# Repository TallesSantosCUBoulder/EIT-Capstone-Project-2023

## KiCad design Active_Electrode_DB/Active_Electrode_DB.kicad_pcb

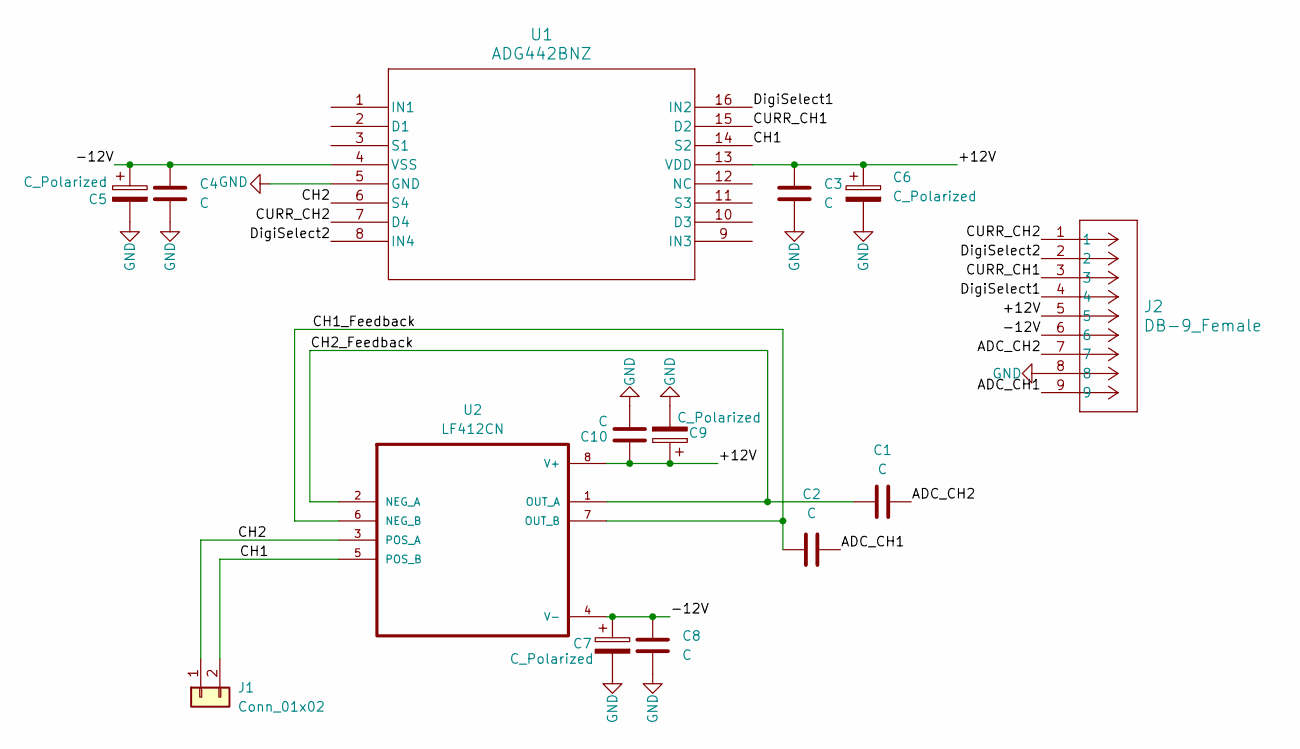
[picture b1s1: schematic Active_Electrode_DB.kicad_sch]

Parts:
C1, C3, C4, C8, C10: C; C_Disc_D4.3mm_W1.9mm_P5.00mm
C2: C; C_Disc_D6.0mm_W2.5mm_P5.00mm
C5, C6, C7, C9: C_Polarized; C_Disc_D4.3mm_W1.9mm_P5.00mm
J1: Conn_01x02; PinSocket_1x02_P2.54mm_Vertical
J2: DB-9_Female
U1: ADG442BNZ; N_16_ADI
U2: LF412CN

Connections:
/+12V: C3.1, C6.1, C9.1, C10.1, J2.5, U1.13 (VDD), U2.8 (V+)
/-12V: C4.1, C5.1, C7.1, C8.1, J2.6, U1.4 (VSS), U2.4 (V-)
/ADC_CH1: C2.2, J2.9
/ADC_CH2: C1.2, J2.7
/CH1: J1.2, U1.14 (S2), U2.5 (POS_B)
/CH1_Feedback: C2.1, U2.6 (NEG_B), U2.7 (OUT_B)
/CH2: J1.1, U1.6 (S4), U2.3 (POS_A)
/CH2_Feedback: C1.1, U2.1 (OUT_A), U2.2 (NEG_A)
/CURR_CH1: J2.3, U1.15 (D2)
/CURR_CH2: J2.1, U1.7 (D4)
/DigiSelect1: J2.4, U1.16 (IN2)
/DigiSelect2: J2.2, U1.8 (IN4)
GND: C3.2, C4.2, C5.2, C6.2, C7.2, C8.2, C9.2, C10.2, J2.8, U1.5 (GND)

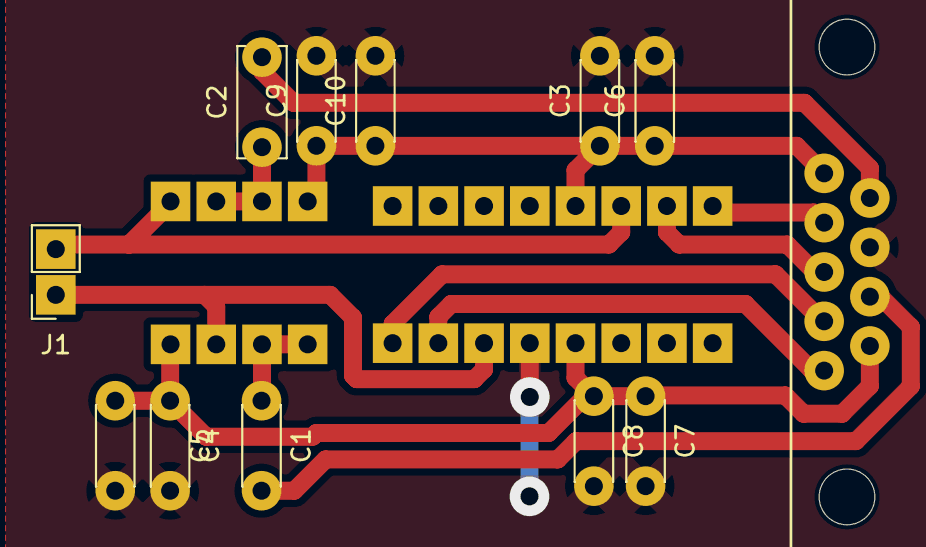
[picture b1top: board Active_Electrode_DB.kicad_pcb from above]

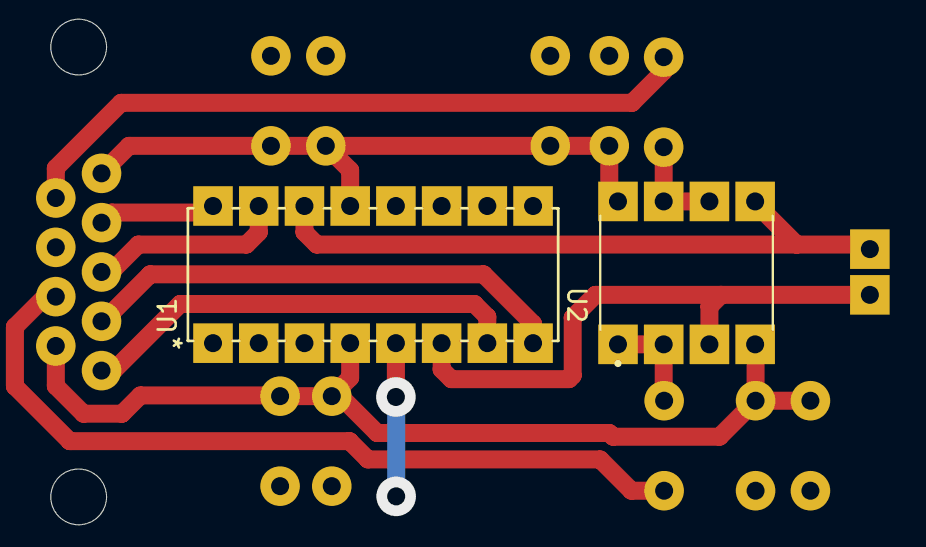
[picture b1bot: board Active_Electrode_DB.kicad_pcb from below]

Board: 2 copper layers, 14 parts (2 on the bottom side), 13 nets.

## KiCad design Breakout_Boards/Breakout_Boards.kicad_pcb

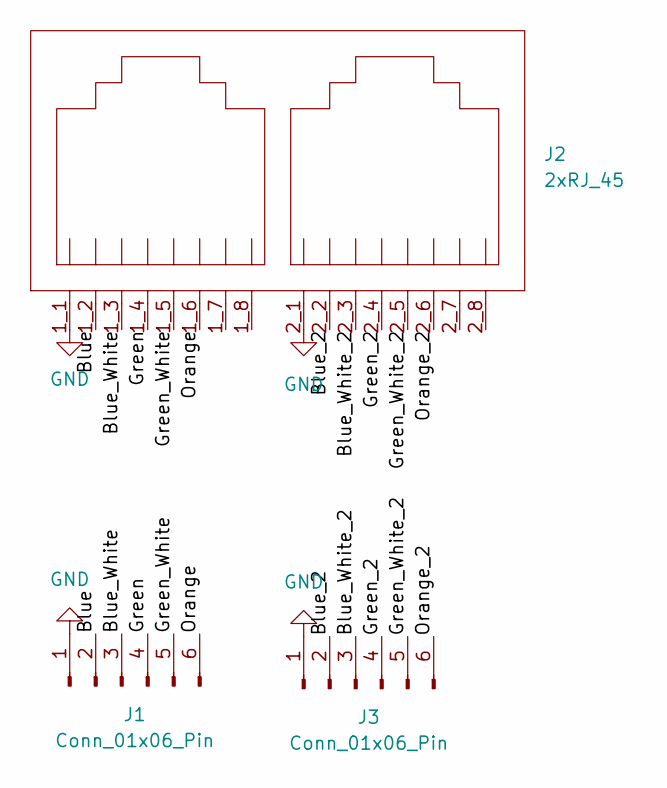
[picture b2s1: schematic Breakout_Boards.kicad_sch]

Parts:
J1, J3: Conn_01x06_Pin; PinSocket_1x06_P2.54mm_Vertical
J2: 2xRJ_45; TE_2xRJ45

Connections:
/Ethernet_Breakout/Blue: J1.2, J2.1_2
/Ethernet_Breakout/Blue_2: J2.2_2, J3.2
/Ethernet_Breakout/Blue_White: J1.3, J2.1_3
/Ethernet_Breakout/Blue_White_2: J2.2_3, J3.3
/Ethernet_Breakout/Green: J1.4, J2.1_4
/Ethernet_Breakout/Green_2: J2.2_4, J3.4
/Ethernet_Breakout/Green_White: J1.5, J2.1_5
/Ethernet_Breakout/Green_White_2: J2.2_5, J3.5
/Ethernet_Breakout/Orange: J1.6, J2.1_6
/Ethernet_Breakout/Orange_2: J2.2_6, J3.6
GND: J1.1, J2.1_1, J2.2_1, J3.1

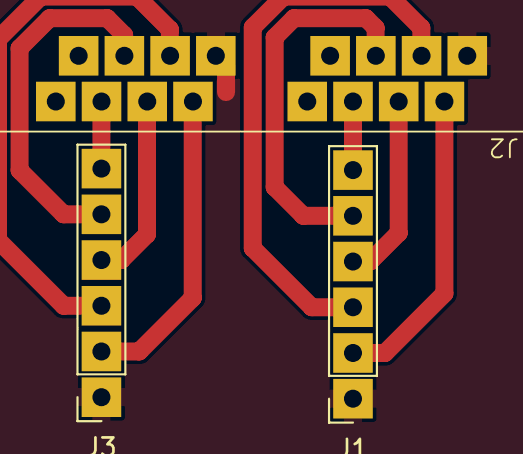
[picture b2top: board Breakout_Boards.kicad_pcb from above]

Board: 2 copper layers, 3 parts (0 on the bottom side), 11 nets.

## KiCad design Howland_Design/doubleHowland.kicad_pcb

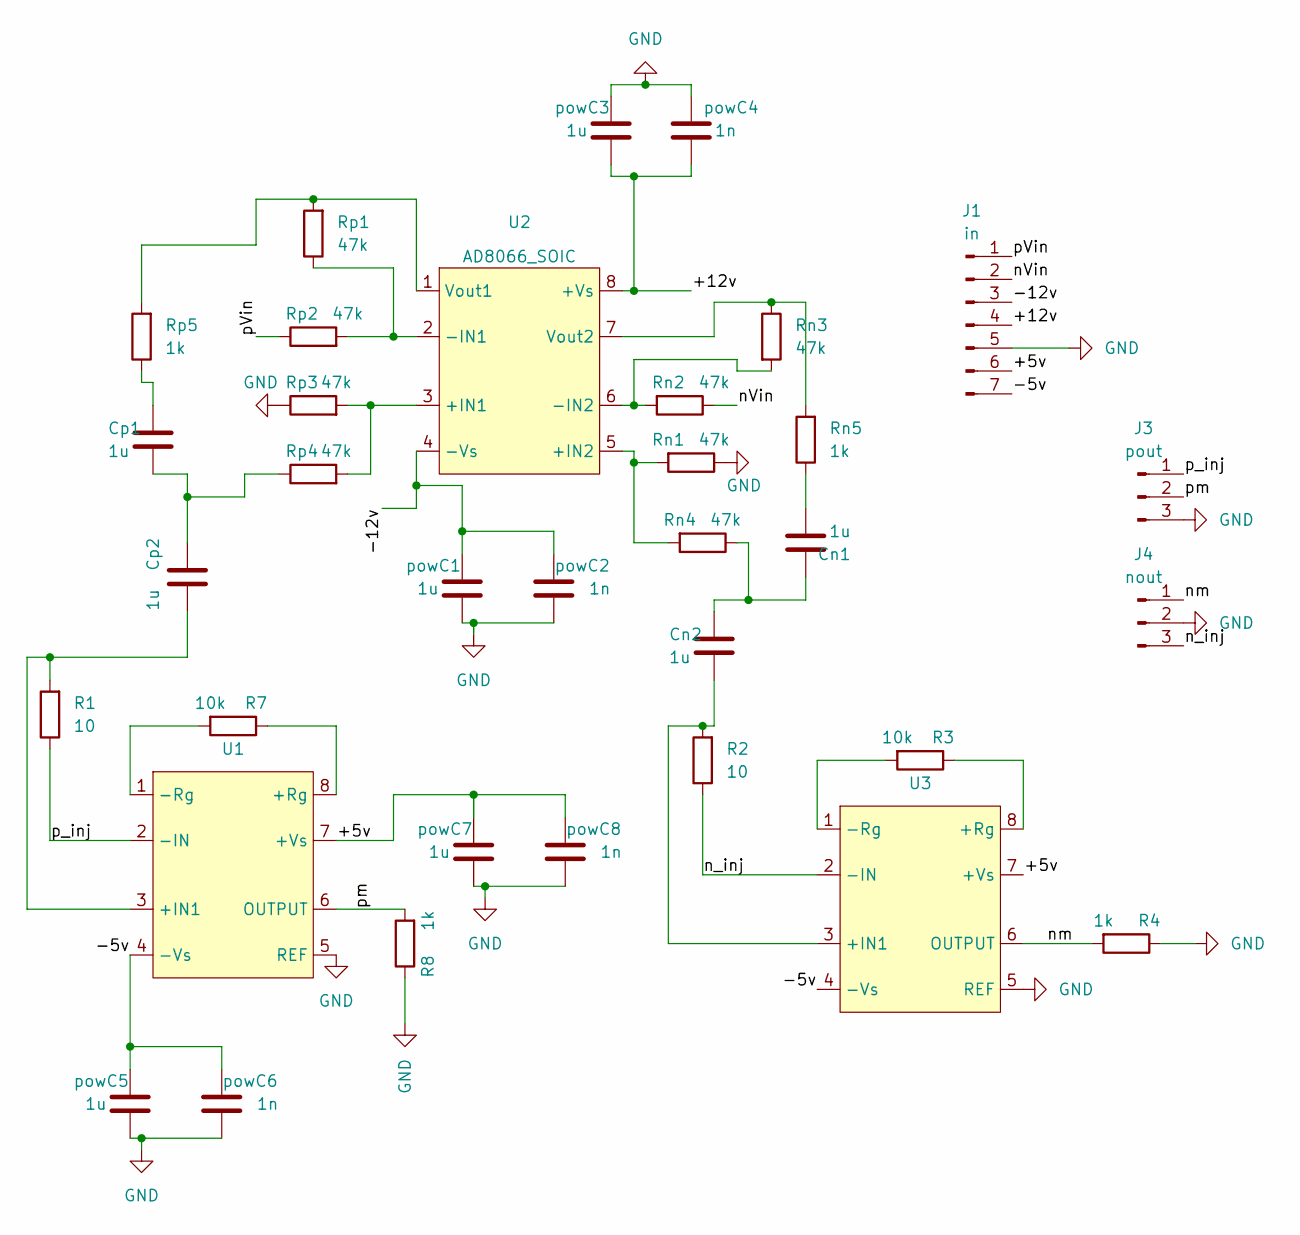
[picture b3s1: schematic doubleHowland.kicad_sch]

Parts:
Cn1, Cn2: 1u; R_Axial_DIN0207_L6.3mm_D2.5mm_P7.62mm_Horizontal
Cp1, Cp2: 1u; R_Axial_DIN0207_L6.3mm_D2.5mm_P7.62mm_Horizontal
J1: in; PinHeader_1x07_P2.54mm_Vertical
J3: pout; PinHeader_1x03_P2.54mm_Vertical
J4: nout; PinHeader_1x03_P2.54mm_Vertical
R1, R2: 10; R_Axial_DIN0207_L6.3mm_D2.5mm_P10.16mm_Horizontal
R3, R7: 10k; R_Axial_DIN0207_L6.3mm_D2.5mm_P10.16mm_Horizontal
R4, R8: 1k; R_Axial_DIN0207_L6.3mm_D2.5mm_P10.16mm_Horizontal
Rn1, Rn2, Rn3, Rn4: 47k; R_Axial_DIN0207_L6.3mm_D2.5mm_P10.16mm_Horizontal
Rn5: 1k; R_Axial_DIN0207_L6.3mm_D2.5mm_P10.16mm_Horizontal
Rp1, Rp2, Rp3, Rp4: 47k; R_Axial_DIN0207_L6.3mm_D2.5mm_P10.16mm_Horizontal
Rp5: 1k; R_Axial_DIN0207_L6.3mm_D2.5mm_P10.16mm_Horizontal
U1, U3: DIP-8_W7.62mm
U2: AD8066_SOIC; DIP-8_W7.62mm
powC1, powC3, powC5, powC7: 1u; R_Axial_DIN0207_L6.3mm_D2.5mm_P7.62mm_Horizontal
powC2, powC4, powC6, powC8: 1n; R_Axial_DIN0207_L6.3mm_D2.5mm_P7.62mm_Horizontal

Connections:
/+5v: J1.6, U1.7 (+Vs), U3.7 (+Vs), powC7.1, powC8.1
/+12v: J1.4, U2.8 (+Vs), powC3.2, powC4.2
/-5v: J1.7, U1.4 (-Vs), U3.4 (-Vs), powC5.1, powC6.1
/-12v: J1.3, U2.4 (-Vs), powC1.1, powC2.1
/nVin: J1.2, Rn2.1
/n_inj: J4.3, R2.1, U3.2 (-IN)
/nm: J4.1, R4.2, U3.6 (OUTPUT)
/pVin: J1.1, Rp2.1
/p_inj: J3.1, R1.1, U1.2 (-IN)
/pm: J3.2, R8.2, U1.6 (OUTPUT)
GND: J1.5, J3.3, J4.2, R4.1, R8.1, Rn1.1, Rp3.1, U1.5 (REF), U3.5 (REF), powC1.2, powC2.2, powC3.1, powC4.1, powC5.2, powC6.2, powC7.2, powC8.2
unnamed: Cn1.1, Cn2.1, Rn4.1
unnamed: Cn1.2, Rn5.1
unnamed: Cp1.1, Rp5.1
unnamed: Cp1.2, Cp2.1, Rp4.1
unnamed: Cp2.2, R1.2, U1.3 (+IN1)
unnamed: R7.1, U1.8 (+Rg)
unnamed: R7.2, U1.1 (-Rg)
unnamed: Rp3.2, Rp4.2, U2.3 (+IN1)
unnamed: Rn1.2, Rn4.2, U2.5 (+IN2)
unnamed: Rp1.1, Rp2.2, U2.2 (-IN1)
unnamed: Rn2.2, Rn3.2, U2.6 (-IN2)
unnamed: Rp1.2, Rp5.2, U2.1 (Vout1)
unnamed: Rn3.1, Rn5.2, U2.7 (Vout2)
unnamed: Cn2.2, R2.2, U3.3 (+IN1)
unnamed: R3.1, U3.8 (+Rg)
unnamed: R3.2, U3.1 (-Rg)

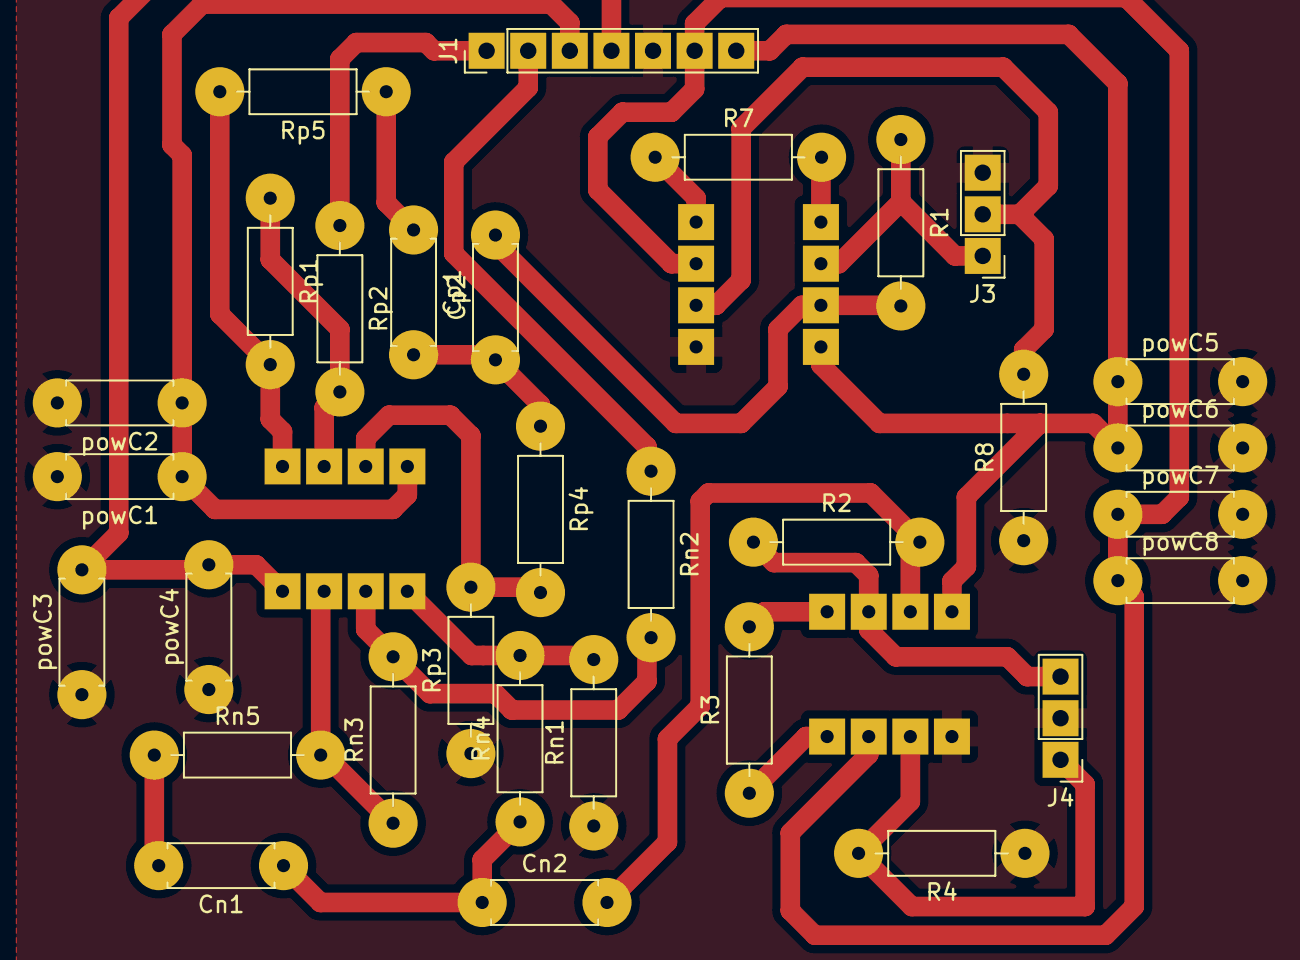
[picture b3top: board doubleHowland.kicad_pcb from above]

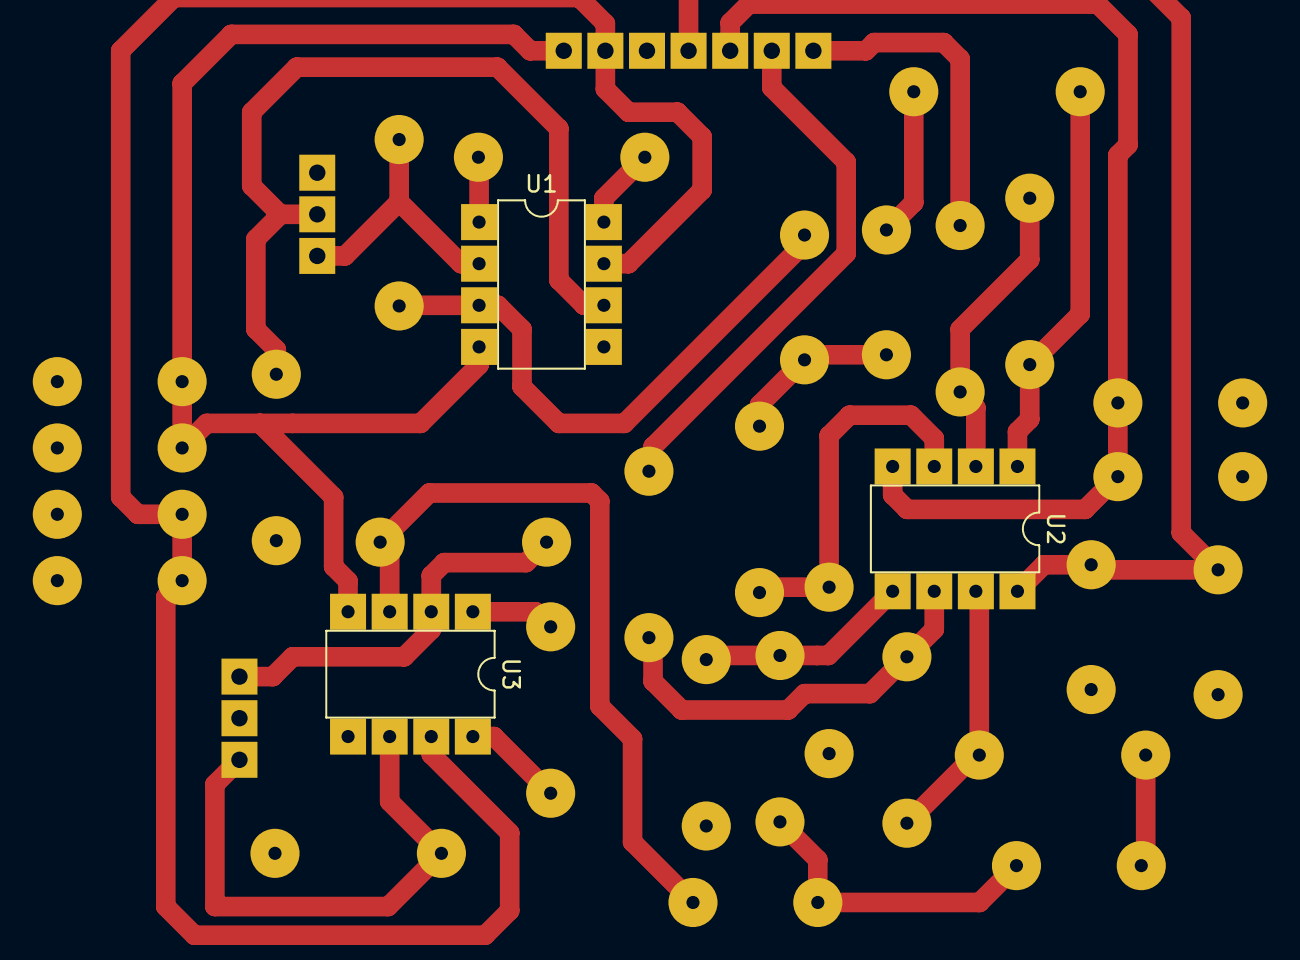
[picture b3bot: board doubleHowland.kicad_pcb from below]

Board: 2 copper layers, 34 parts (3 on the bottom side), 27 nets.

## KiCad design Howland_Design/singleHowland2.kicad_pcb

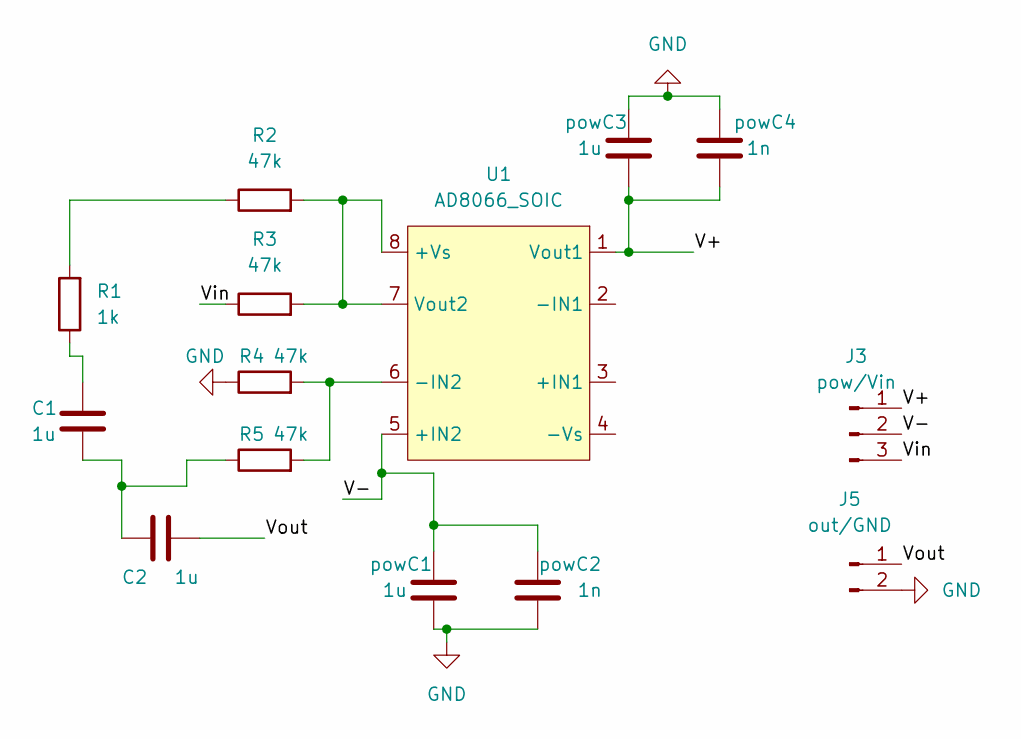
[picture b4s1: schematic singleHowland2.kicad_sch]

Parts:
C1, C2: 1u; R_Axial_DIN0207_L6.3mm_D2.5mm_P7.62mm_Horizontal
J3: pow/Vin; PinHeader_1x03_P2.54mm_Vertical
J5: out/GND; PinHeader_1x02_P2.54mm_Vertical
R1: 1k; R_Axial_DIN0207_L6.3mm_D2.5mm_P7.62mm_Horizontal
R2, R3, R4, R5: 47k; R_Axial_DIN0207_L6.3mm_D2.5mm_P7.62mm_Horizontal
U1: AD8066_SOIC; DIP-8_W7.62mm
powC1, powC3: 1u; R_Axial_DIN0207_L6.3mm_D2.5mm_P7.62mm_Horizontal
powC2, powC4: 1n; R_Axial_DIN0207_L6.3mm_D2.5mm_P7.62mm_Horizontal

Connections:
/V+: J3.1, U1.1 (Vout1), powC3.2, powC4.2
/V-: J3.2, U1.5 (+IN2), powC1.1, powC2.1
/Vin: J3.3, R3.1
/Vout: C2.2, J5.1
GND: J5.2, R4.1, powC1.2, powC2.2, powC3.1, powC4.1
unnamed: C1.1, R1.1
unnamed: C1.2, C2.1, R5.1
unnamed: R1.2, R2.1
unnamed: R2.2, R3.2, U1.7 (Vout2), U1.8 (+Vs)
unnamed: R4.2, R5.2, U1.6 (-IN2)

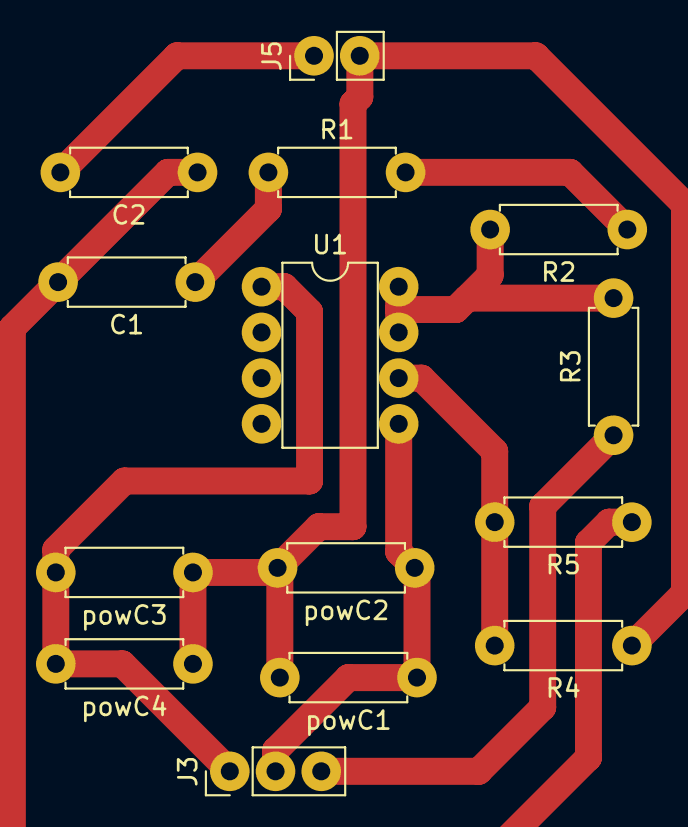
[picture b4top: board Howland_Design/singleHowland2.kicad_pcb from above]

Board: 2 copper layers, 14 parts (0 on the bottom side), 10 nets.

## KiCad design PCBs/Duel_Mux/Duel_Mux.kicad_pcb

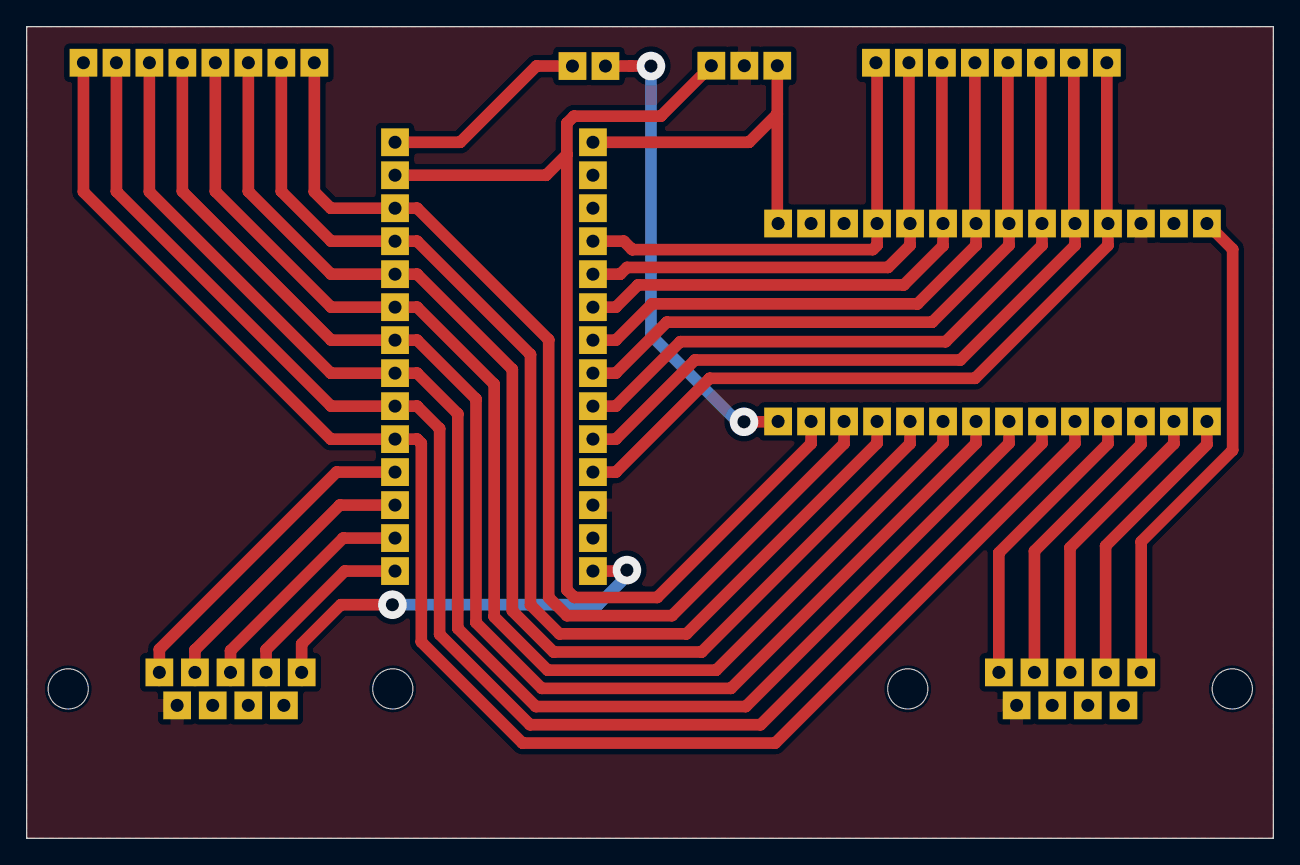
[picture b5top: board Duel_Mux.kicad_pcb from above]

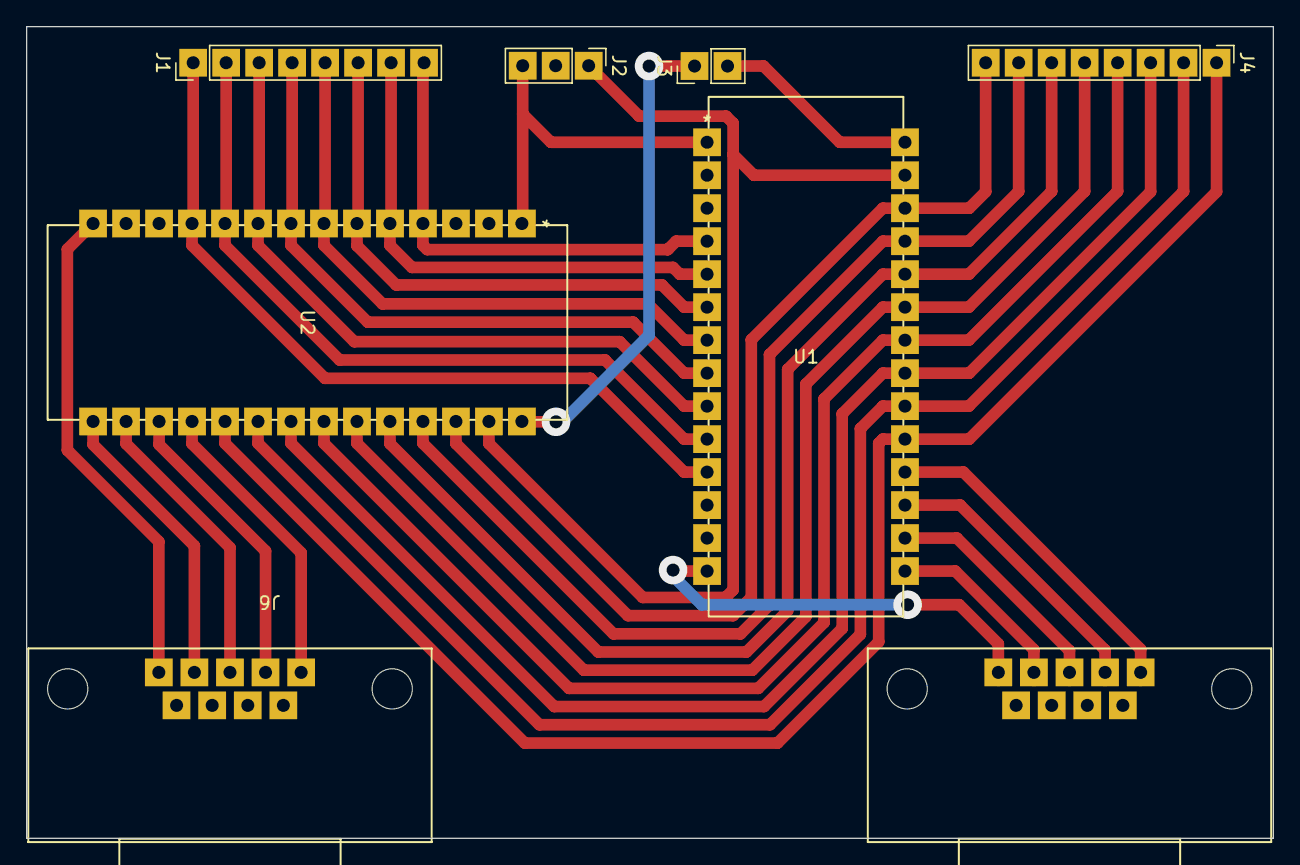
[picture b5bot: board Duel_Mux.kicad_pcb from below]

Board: 2 copper layers, 96.0 x 62.5 mm, 8 parts (8 on the bottom side), 31 nets.

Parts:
J1, J4: Conn_01x08_Pin; PinHeader_1x08_P2.54mm_Vertical
J2: Conn_01x03_Pin; PinHeader_1x03_P2.54mm_Vertical
J3: Conn_01x02_Pin; PinHeader_1x02_P2.54mm_Vertical
J5, J6: DB-9_Female
U1, U2: ADG406BNZ

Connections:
/+12V: J2.3, U1.1 (VDD), U2.1 (VDD)
/-12V: J2.1, U1.27 (VSS), U2.27 (VSS)
/A0_1: J6.4, U2.17 (A0)
/A0_2: J5.4, U1.17 (A0)
/A1_1: J6.3, U2.16 (A1)
/A1_2: J5.3, U1.16 (A1)
/A2_1: J6.2, U2.15 (A2)
/A2_2: J5.2, U1.15 (A2)
/A3_1: J6.1, U2.14 (A3)
/A3_2: J5.1, U1.14 (A3)
/CH1: J4.1, U1.19 (S1), U2.19 (S1)
/CH2: J4.2, U1.20 (S2), U2.20 (S2)
/CH3: J4.3, U1.21 (S3), U2.21 (S3)
/CH4: J4.4, U1.22 (S4), U2.22 (S4)
/CH5: J4.5, U1.23 (S5), U2.23 (S5)
/CH6: J4.6, U1.24 (S6), U2.24 (S6)
/CH7: J4.7, U1.25 (S7), U2.25 (S7)
/CH8: J4.8, U1.26 (S8), U2.26 (S8)
/CH9: J1.1, U1.11 (S9), U2.11 (S9)
/CH10: J1.2, U1.10 (S10), U2.10 (S10)
/CH11: J1.3, U1.9 (S11), U2.9 (S11)
/CH12: J1.4, U1.8 (S12), U2.8 (S12)
/CH13: J1.5, U1.7 (S13), U2.7 (S13)
/CH14: J1.6, U1.6 (S14), U2.6 (S14)
/CH15: J1.7, U1.5 (S15), U2.5 (S15)
/CH16: J1.8, U1.4 (S16), U2.4 (S16)
/D1: J3.1, U2.28 (D)
/D2: J3.2, U1.28 (D)
/EN_1: J6.5, U2.18 (EN)
/EN_2: J5.5, U1.18 (EN)
GND: J2.2, J5.9, J6.9, U1.12 (GND), U2.12 (GND)

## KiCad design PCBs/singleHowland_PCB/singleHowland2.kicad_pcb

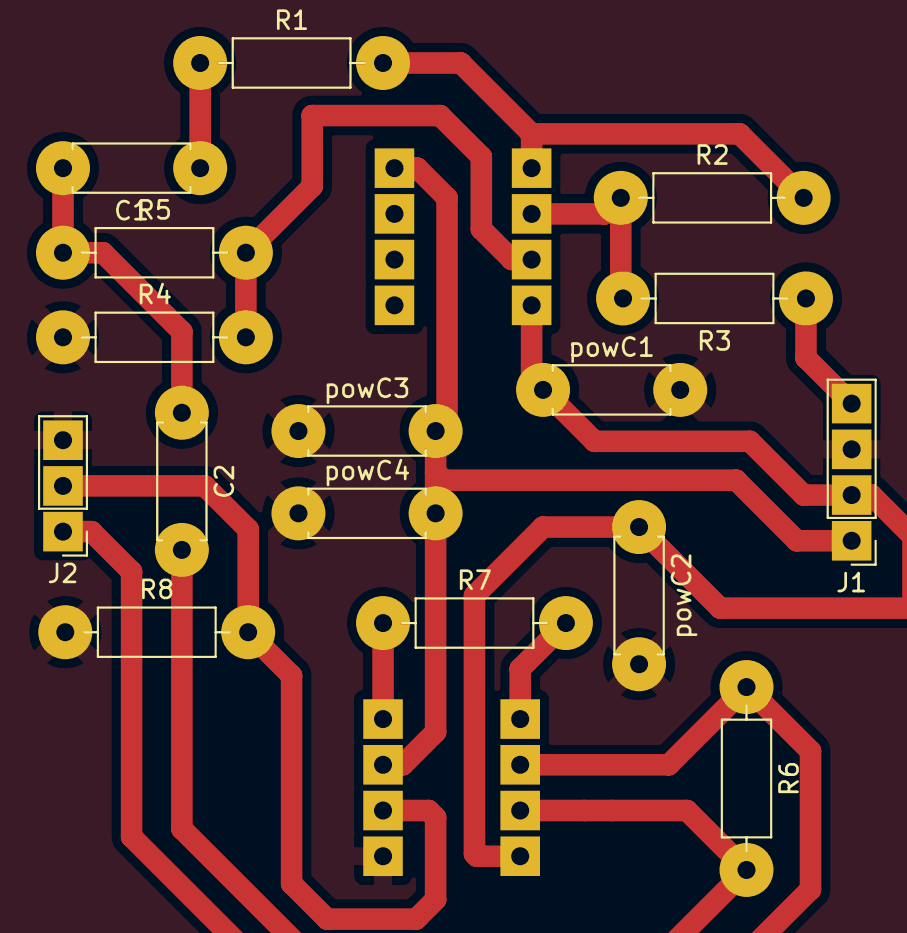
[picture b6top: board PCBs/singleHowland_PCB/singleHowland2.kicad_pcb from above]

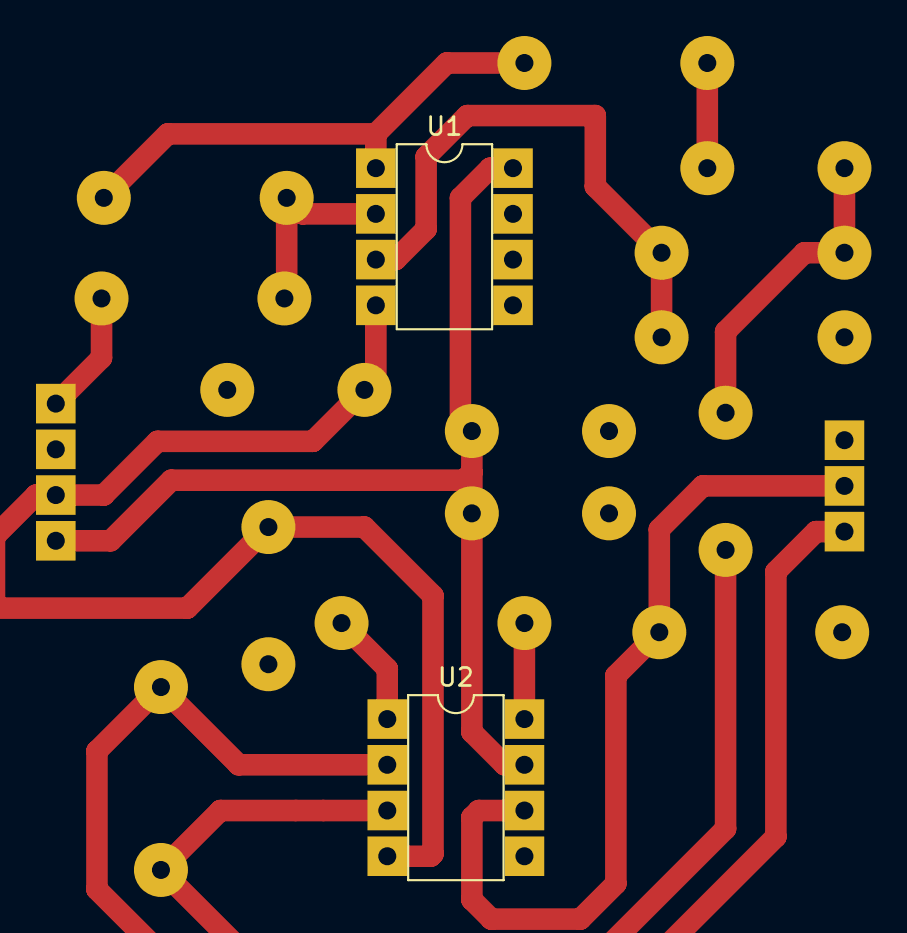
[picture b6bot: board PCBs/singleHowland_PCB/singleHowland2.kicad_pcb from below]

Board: 2 copper layers, 18 parts (2 on the bottom side), 14 nets.

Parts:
C1, C2: 1u; R_Axial_DIN0207_L6.3mm_D2.5mm_P7.62mm_Horizontal
J1: pow/Vin; PinHeader_1x04_P2.54mm_Vertical
J2: Conn_01x03_Pin; PinHeader_1x03_P2.54mm_Vertical
R1: 1k; R_Axial_DIN0207_L6.3mm_D2.5mm_P10.16mm_Horizontal
R2, R3, R4, R5: 47k; R_Axial_DIN0207_L6.3mm_D2.5mm_P10.16mm_Horizontal
R6: 10; R_Axial_DIN0207_L6.3mm_D2.5mm_P10.16mm_Horizontal
R7: 500; R_Axial_DIN0207_L6.3mm_D2.5mm_P10.16mm_Horizontal
R8: 10k; R_Axial_DIN0207_L6.3mm_D2.5mm_P10.16mm_Horizontal
U1: AD8066_SOIC; DIP-8_W7.62mm
U2: DIP-8_W7.62mm
powC1, powC3: 1u; R_Axial_DIN0207_L6.3mm_D2.5mm_P7.62mm_Horizontal
powC2, powC4: 1n; R_Axial_DIN0207_L6.3mm_D2.5mm_P7.62mm_Horizontal

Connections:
/Injection: J2.1, R6.1, U2.2 (-IN)
/V+: J1.1, U1.8 (+Vs), U2.7 (+Vs), powC3.2, powC4.2
/V-: J1.2, U1.4 (-Vs), U2.4 (-Vs), powC1.1, powC2.1
/Vin: J1.4, R3.1
/m+: J2.2, R8.2, U2.6 (OUTPUT)
GND: J1.3, J2.3, R4.1, R8.1, U2.5 (REF), powC1.2, powC2.2, powC3.1, powC4.1
unnamed: C1.1, R1.1
unnamed: C1.2, C2.1, R5.1
unnamed: R4.2, R5.2, U1.3 (+IN1)
unnamed: R2.1, R3.2, U1.2 (-IN1)
unnamed: R1.2, R2.2, U1.1 (Vout1)
unnamed: C2.2, R6.2, U2.3 (+IN1)
unnamed: R7.1, U2.8 (+Rg)
unnamed: R7.2, U2.1 (-Rg)
